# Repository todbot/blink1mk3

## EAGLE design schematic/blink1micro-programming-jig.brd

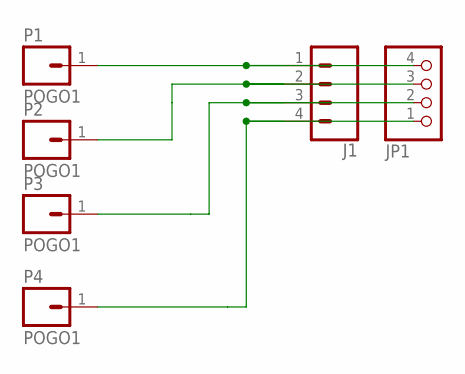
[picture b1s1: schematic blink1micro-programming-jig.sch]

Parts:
J1: CONN_04; 1X04
JP1: PINHD-1X4/90; 1X04/90
P1, P2, P3, P4: POGO1; MILLMAX-0928-POGO-THRU

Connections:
unnamed: J1.1, JP1.4, P1.1
unnamed: J1.2, JP1.3, P2.1
unnamed: J1.3, JP1.2, P3.1
unnamed: J1.4, JP1.1, P4.1

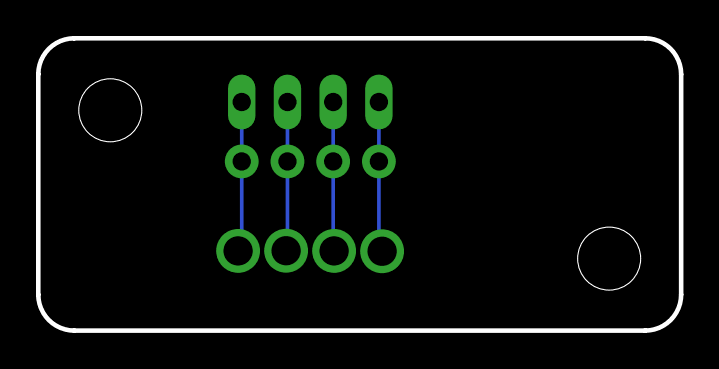
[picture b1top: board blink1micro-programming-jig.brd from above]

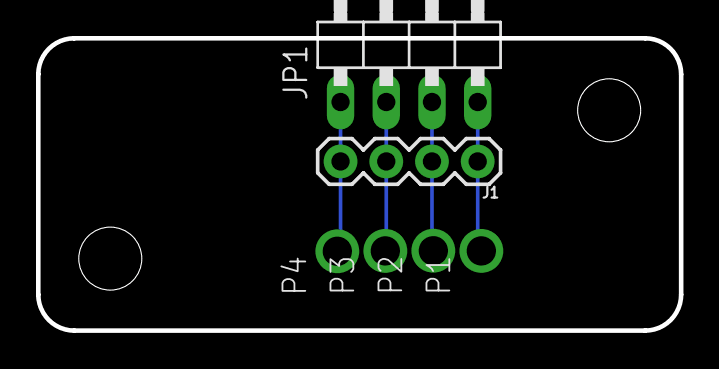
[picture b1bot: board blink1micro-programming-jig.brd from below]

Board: 2 copper layers, 35.7 x 16.2 mm, 6 parts (6 on the bottom side), 4 nets.

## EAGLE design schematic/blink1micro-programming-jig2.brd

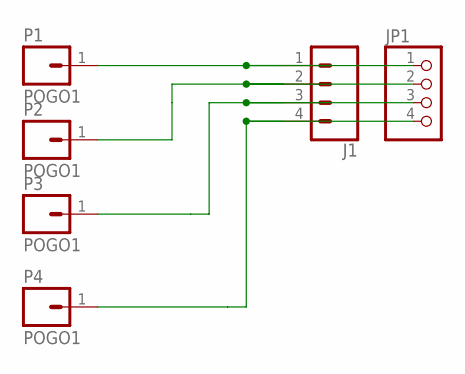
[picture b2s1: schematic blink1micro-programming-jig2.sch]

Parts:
J1: CONN_04; 1X04
JP1: PINHD-1X4/90; 1X04/90
P1, P2, P3, P4: POGO1; MILLMAX-0928-POGO-THRU

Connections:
unnamed: J1.1, JP1.1, P1.1
unnamed: J1.2, JP1.2, P2.1
unnamed: J1.3, JP1.3, P3.1
unnamed: J1.4, JP1.4, P4.1

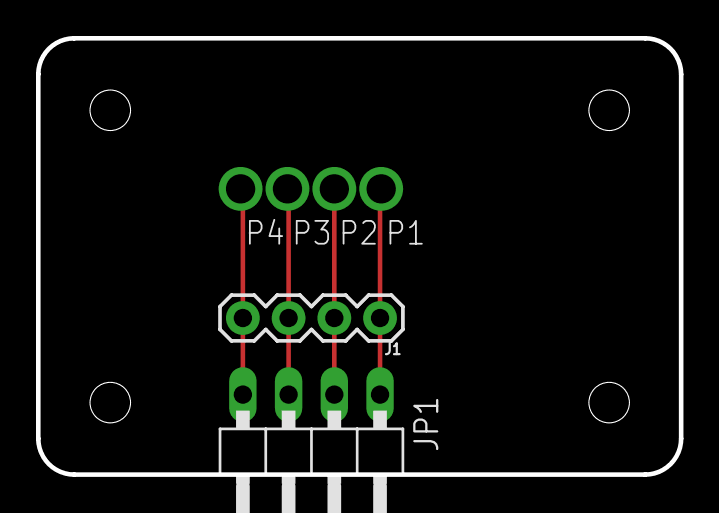
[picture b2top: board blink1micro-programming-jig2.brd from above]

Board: 2 copper layers, 35.7 x 24.2 mm, 6 parts (0 on the bottom side), 4 nets.

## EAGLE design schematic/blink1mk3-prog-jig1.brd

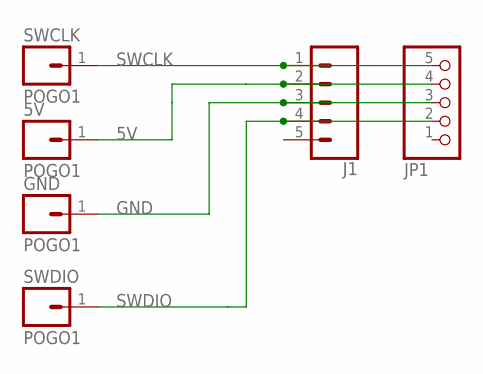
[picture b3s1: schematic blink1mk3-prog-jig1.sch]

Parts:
5V: POGO1; MILLMAX-0928-POGO-THRU
GND: POGO1; MILLMAX-0928-POGO-THRU
J1: CONN_05; 1X05
JP1: PINHD-1X5/90; 1X05/90
SWCLK: POGO1; MILLMAX-0928-POGO-THRU
SWDIO: POGO1; MILLMAX-0928-POGO-THRU

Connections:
5V: 5V.1, J1.2, JP1.4
GND: GND.1, J1.3, JP1.3
SWCLK: J1.1, JP1.5, SWCLK.1
SWDIO: J1.4, JP1.2, SWDIO.1

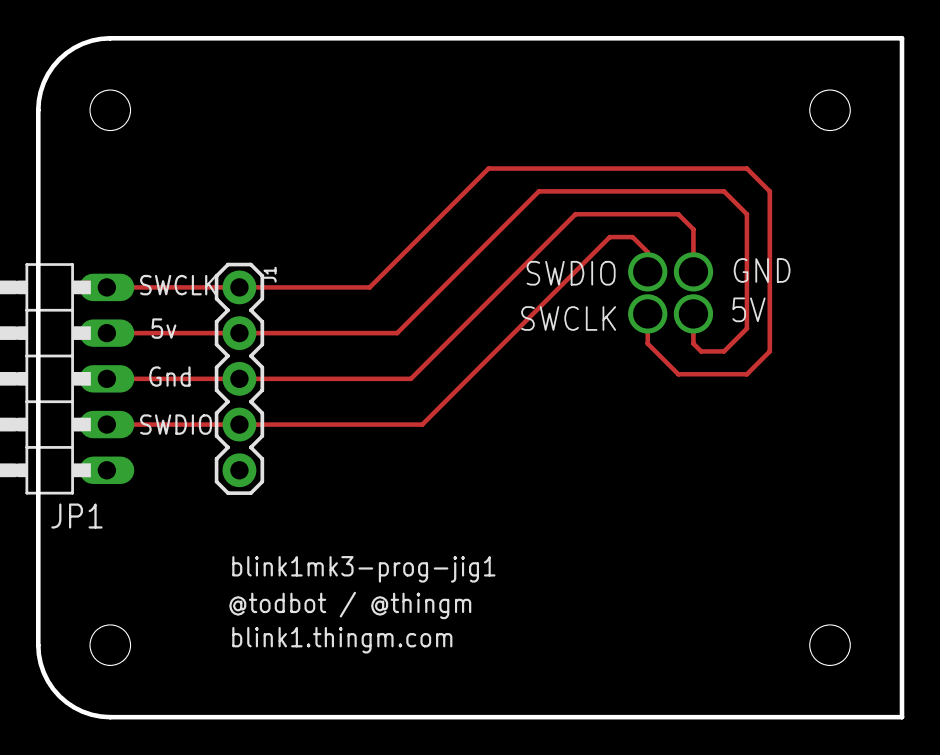
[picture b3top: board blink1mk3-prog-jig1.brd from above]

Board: 2 copper layers, 48.0 x 37.7 mm, 6 parts (0 on the bottom side), 4 nets.

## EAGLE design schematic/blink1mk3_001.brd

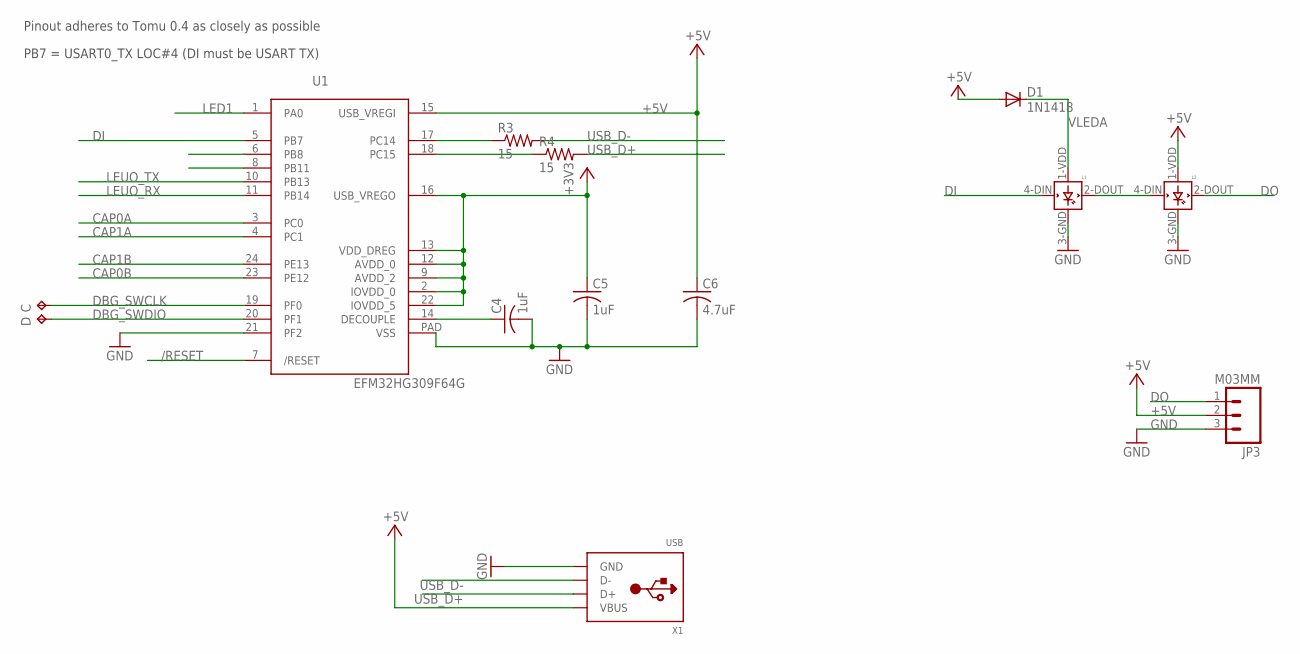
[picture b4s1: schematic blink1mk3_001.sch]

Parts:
C: TPTP10R; TP10R
C4, C5: 1uF; C0402
C6: 4.7uF; C0402
D: TPTP10R; TP10R
D1: 1N1418; SOD523
JP3: M03MM; 1X03-1.5MM
L1, L2: WS2812B
R3, R4: 15; R0402
U1: EFM32HG309F64G; QFN24PAD
X1: USB; MOLEX-48037-1000

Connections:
+3V3: C5.1, U1.2 (IOVDD_0), U1.9 (AVDD_2), U1.12 (AVDD_0), U1.13 (VDD_DREG), U1.16 (USB_VREGO), U1.22 (IOVDD_5)
+5V: C6.1, D1.A, JP3.2, L2.1-VDD (VDD), U1.15 (USB_VREGI), X1.1 (VBUS)
/RESET: U1.7 (/RESET)
CAP0A: U1.3 (PC0)
CAP0B: U1.23 (PE12)
CAP1A: U1.4 (PC1)
CAP1B: U1.24 (PE13)
DBG_SWCLK: C.TP, U1.19 (PF0)
DBG_SWDIO: D.TP, U1.20 (PF1)
DECOUPLE: C4.1, U1.14 (DECOUPLE)
DI: L1.4-DIN (DIN), U1.5 (PB7)
DO: JP3.1, L2.2-DOUT (DOUT)
GND: C4.2, C5.2, C6.2, JP3.3, L1.3-GND (GND), L2.3-GND (GND), U1.21 (PF2), U1.PAD (VSS), X1.4 (GND)
LED1: U1.1 (PA0)
LEUO_RX: U1.11 (PB14)
LEUO_TX: U1.10 (PB13)
unnamed: L1.2-DOUT (DOUT), L2.4-DIN (DIN)
RUSB_D+: R4.1, U1.18 (PC15)
RUSB_D-: R3.1, U1.17 (PC14)
USB_D+: R4.2, X1.3 (D+)
USB_D-: R3.2, X1.2 (D-)
VLEDA: D1.C, L1.1-VDD (VDD)

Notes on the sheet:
PB7 = USART0_TX LOC#4 (DI must be USART TX)
Pinout adheres to Tomu 0.4 as closely as possible

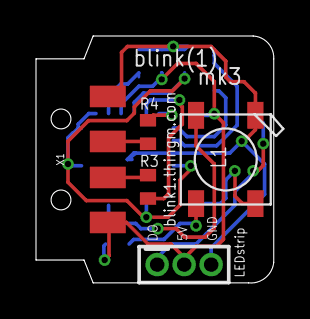
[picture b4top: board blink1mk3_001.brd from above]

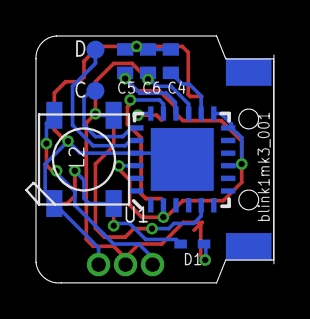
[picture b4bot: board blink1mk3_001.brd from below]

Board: 2 copper layers, 13.2 x 13.7 mm, 13 parts (8 on the bottom side), 14 nets.

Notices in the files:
parts and their libraries:
SparkFun-Connectors: Licensing: Creative Commons ShareAlike 4.0 International - https://creativecommons.org/licenses/by-sa/4.0
